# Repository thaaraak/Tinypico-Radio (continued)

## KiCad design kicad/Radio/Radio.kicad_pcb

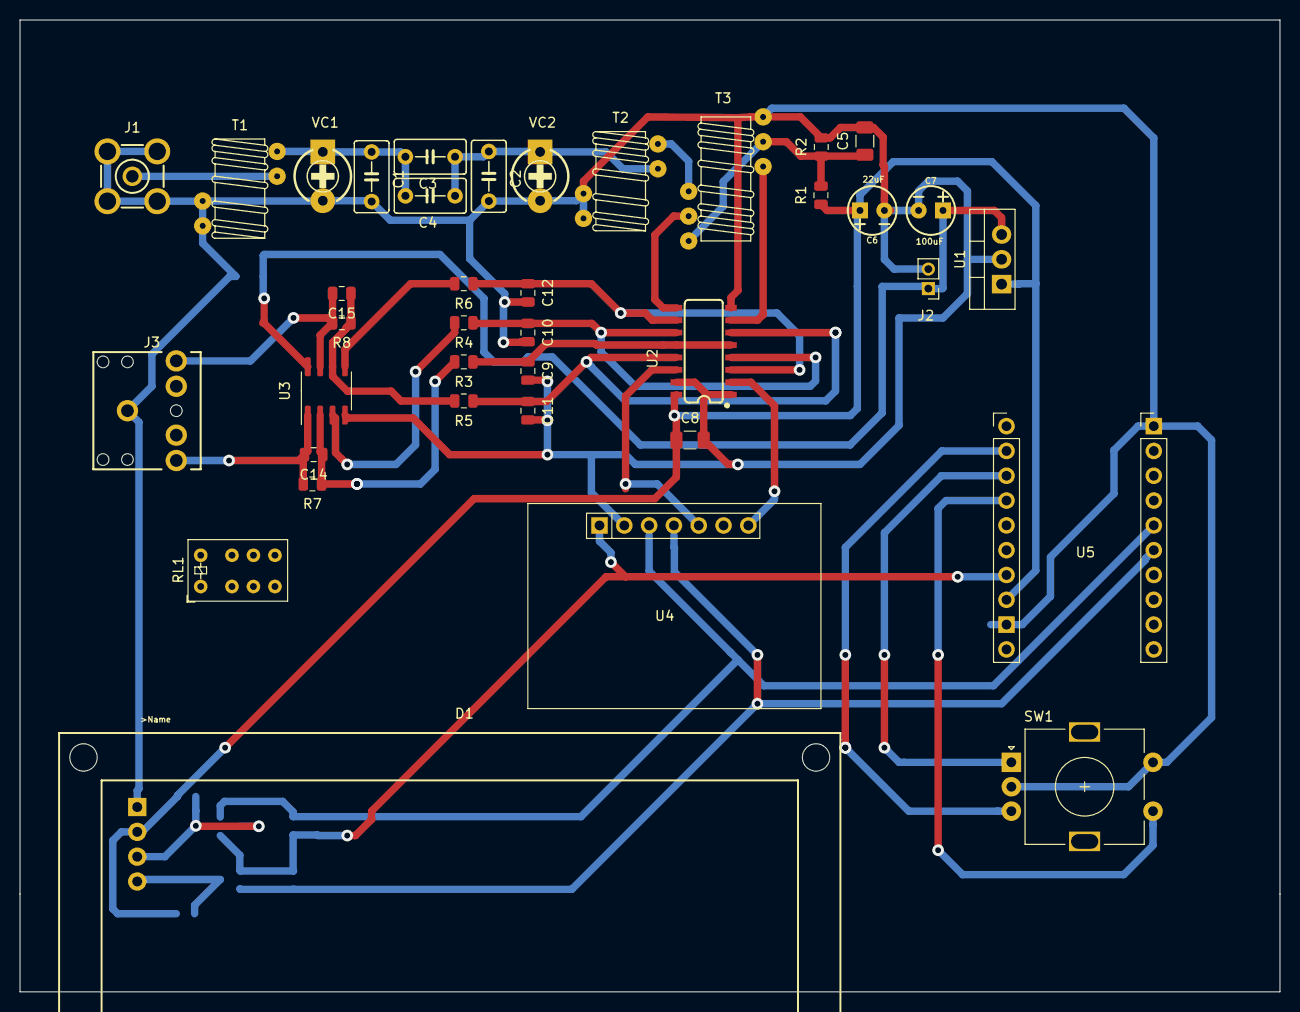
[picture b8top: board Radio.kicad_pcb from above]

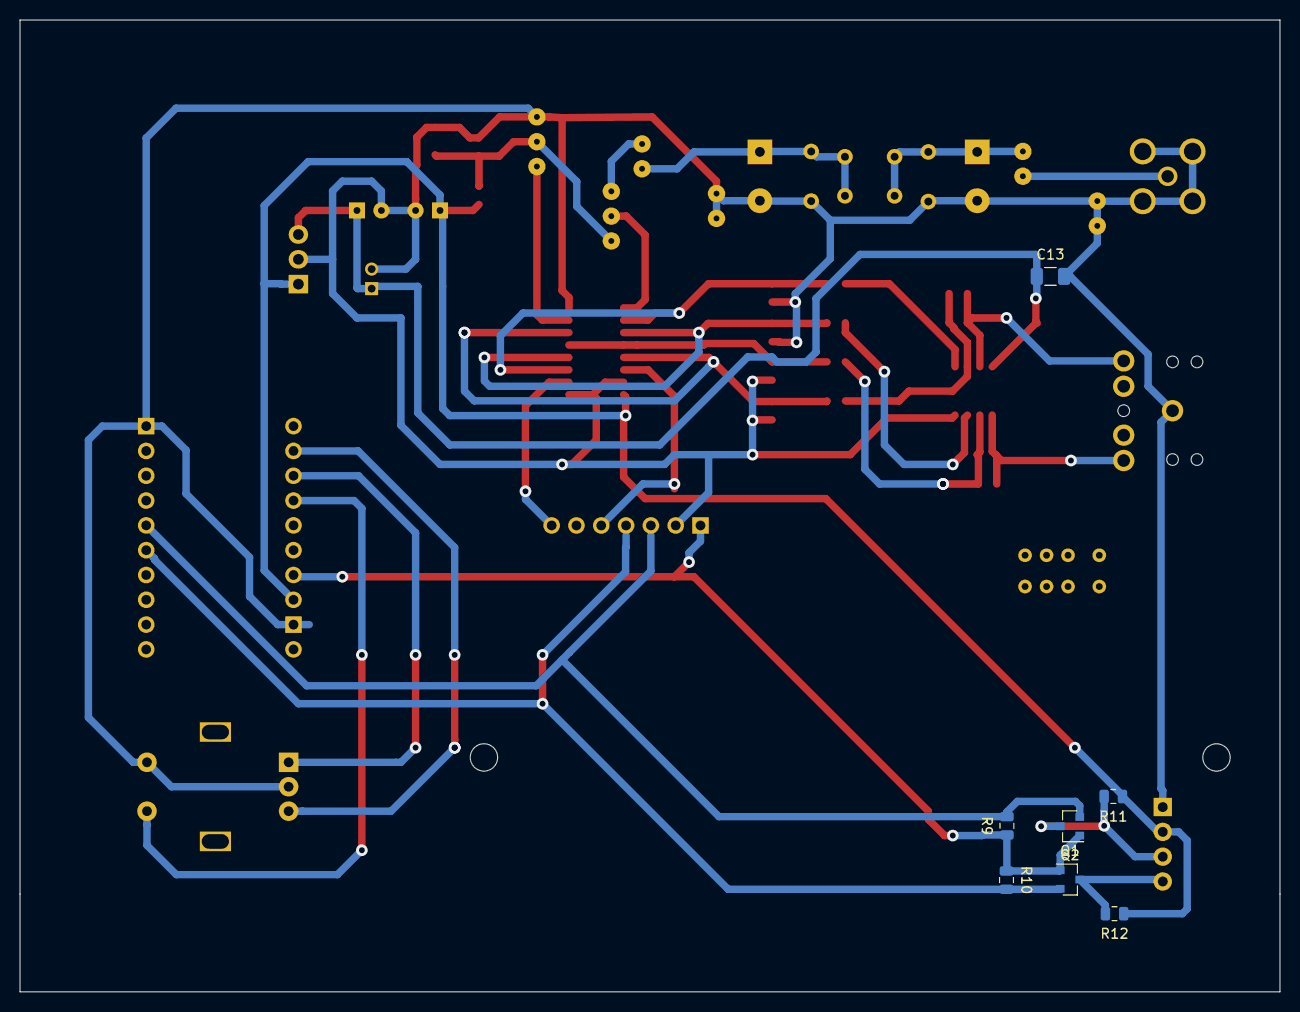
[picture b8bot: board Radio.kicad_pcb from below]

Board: 2 copper layers, 129.0 x 99.5 mm, 45 parts (7 on the bottom side), 30 nets.

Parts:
C1, C2: 150pF; Capacitor
C3: 5pF; Capacitor
C4: 10pF; Capacitor
C5, C8, C13: .1uF; Capacitor 1206
C6: 22uF; CPOL-RADIAL-2.5MM-5MM
C7: 100uF; CPOL-RADIAL-2.5MM-5MM
C9, C10, C11, C12: 470nF; Capacitor 0805
C14, C15: 1nF; Capacitor 0805
D1: LCD_I2C
J1: PCB_SMA; PCB SMA
J2: Conn_01x02; Power Connector
J3: Audio_Jack
Q1, Q2: MOSFET-NCH-AO3404A; SOT-23
R1, R2, R7, R8: 10k; Capacitor 0805
R3, R4, R5, R6: 100; Capacitor 0805
R9, R10, R11, R12: 1k; Capacitor 0805
RL1: JW2; Relay_DPDT_AXICOM_IMSeries_Pitch3.2mm
SW1: Rotary_Encoder_Switch; RotaryEncoder_Alps_EC11E-Switch_Vertical_H20mm
T1: 6:31; T37 Transformer
T2: 31:6; T37 Transformer
T3: T50_SPLITTER; T50 Trifilar
U1: LM7805_TO220; TO-220-3_Vertical
U2: FST3253; SO16
U3: LM358; SOIC8
U4: si5351
U5: TINYPico; TINYpico
VC1, VC2: 40pF; trimcap

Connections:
+3V3: Q1.1, Q2.1, R9.1, R10.1, U4.VIN, U5.3V3
+5V: C6.1, C8.1, D1.2, R1.1, R11.1, R12.1, U1.1, U2.16, U5.5V
+12V: C7.1, C13.1, J2.1, U1.3, U3.8
GND: C1.2, C2.2, C5.2, C6.2, C7.2, C8.2, C9.2, C10.2, C11.2, C12.2, C13.2, D1.1, J1.2, J1.3, J1.4, J1.5, J2.2, J3.SLEEVE, R2.2, SW1.C, SW1.S2, T1.C1A, T1.C2A, T2.C1A, T2.C2A, T3.C1A, U1.2, U2.1, U2.8, U2.15, U3.4, U4.GND, U5.GND, VC1.2, VC2.2
I_OUTPUT: C14.2, J3.TIP, R7.2, U3.1
unnamed: C1.1, C3.2, C4.2, T1.C2B, VC1.1
unnamed: C2.1, C3.1, C4.1, T2.C1B, VC2.1
unnamed: C5.1, R1.2, R2.1, T3.C2A, T3.C3B
unnamed: C9.1, R3.1, U2.5, U2.12
unnamed: C10.1, R4.1, U2.4, U2.11
unnamed: C11.1, R5.1, U2.6, U2.13
unnamed: C12.1, R6.1, U2.3, U2.10
unnamed: C14.1, R3.2, R7.1, U3.2
unnamed: C15.1, R5.2, R8.1, U3.6
unnamed: J1.1, T1.C1B
unnamed: R4.2, U3.3
unnamed: R6.2, U3.5
unnamed: SW1.A, U5.27
unnamed: SW1.B, U5.26
unnamed: SW1.S1, U5.15
unnamed: T2.C2B, T3.C1B
unnamed: T3.C2B, U2.9
unnamed: T3.C3A, U2.7
unnamed: U2.2, U4.0
unnamed: U2.14, U4.2
Q_OUTPUT: C15.2, J3.RING, R8.2, U3.7
SCL_HV: D1.4, Q2.3, R12.2
SCL_LV: Q2.2, R10.2, U4.SCL, U5.22
SDA_HV: D1.3, Q1.3, R11.2
SDA_LV: Q1.2, R9.2, U4.SDA, U5.21

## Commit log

2020-04-11 Copying from pi 4
2020-04-13 Added Tayloe
2020-04-14 Added ADS1115
2020-04-14 Commented out prints
2020-04-20 adding kicad
2020-04-27 Tinypico on board
2020-04-28 Trying to get rid of clicks
2020-04-29 Solved the clicks with Encoder
2020-05-01 Added Phase Shifter
2020-05-01 fix kicad
2020-05-06 fixing cap placement
2020-05-06 added bom
2020-05-06 added BOM and pdf schem,atic
2020-05-07 Added PDF for schematic
2020-05-09 added flter
2020-05-09 added board and schematic for receiver
2020-05-12 adding transmitter
2020-05-24 added PDFs
2020-05-25 replace T
2020-05-31 added mic amp
